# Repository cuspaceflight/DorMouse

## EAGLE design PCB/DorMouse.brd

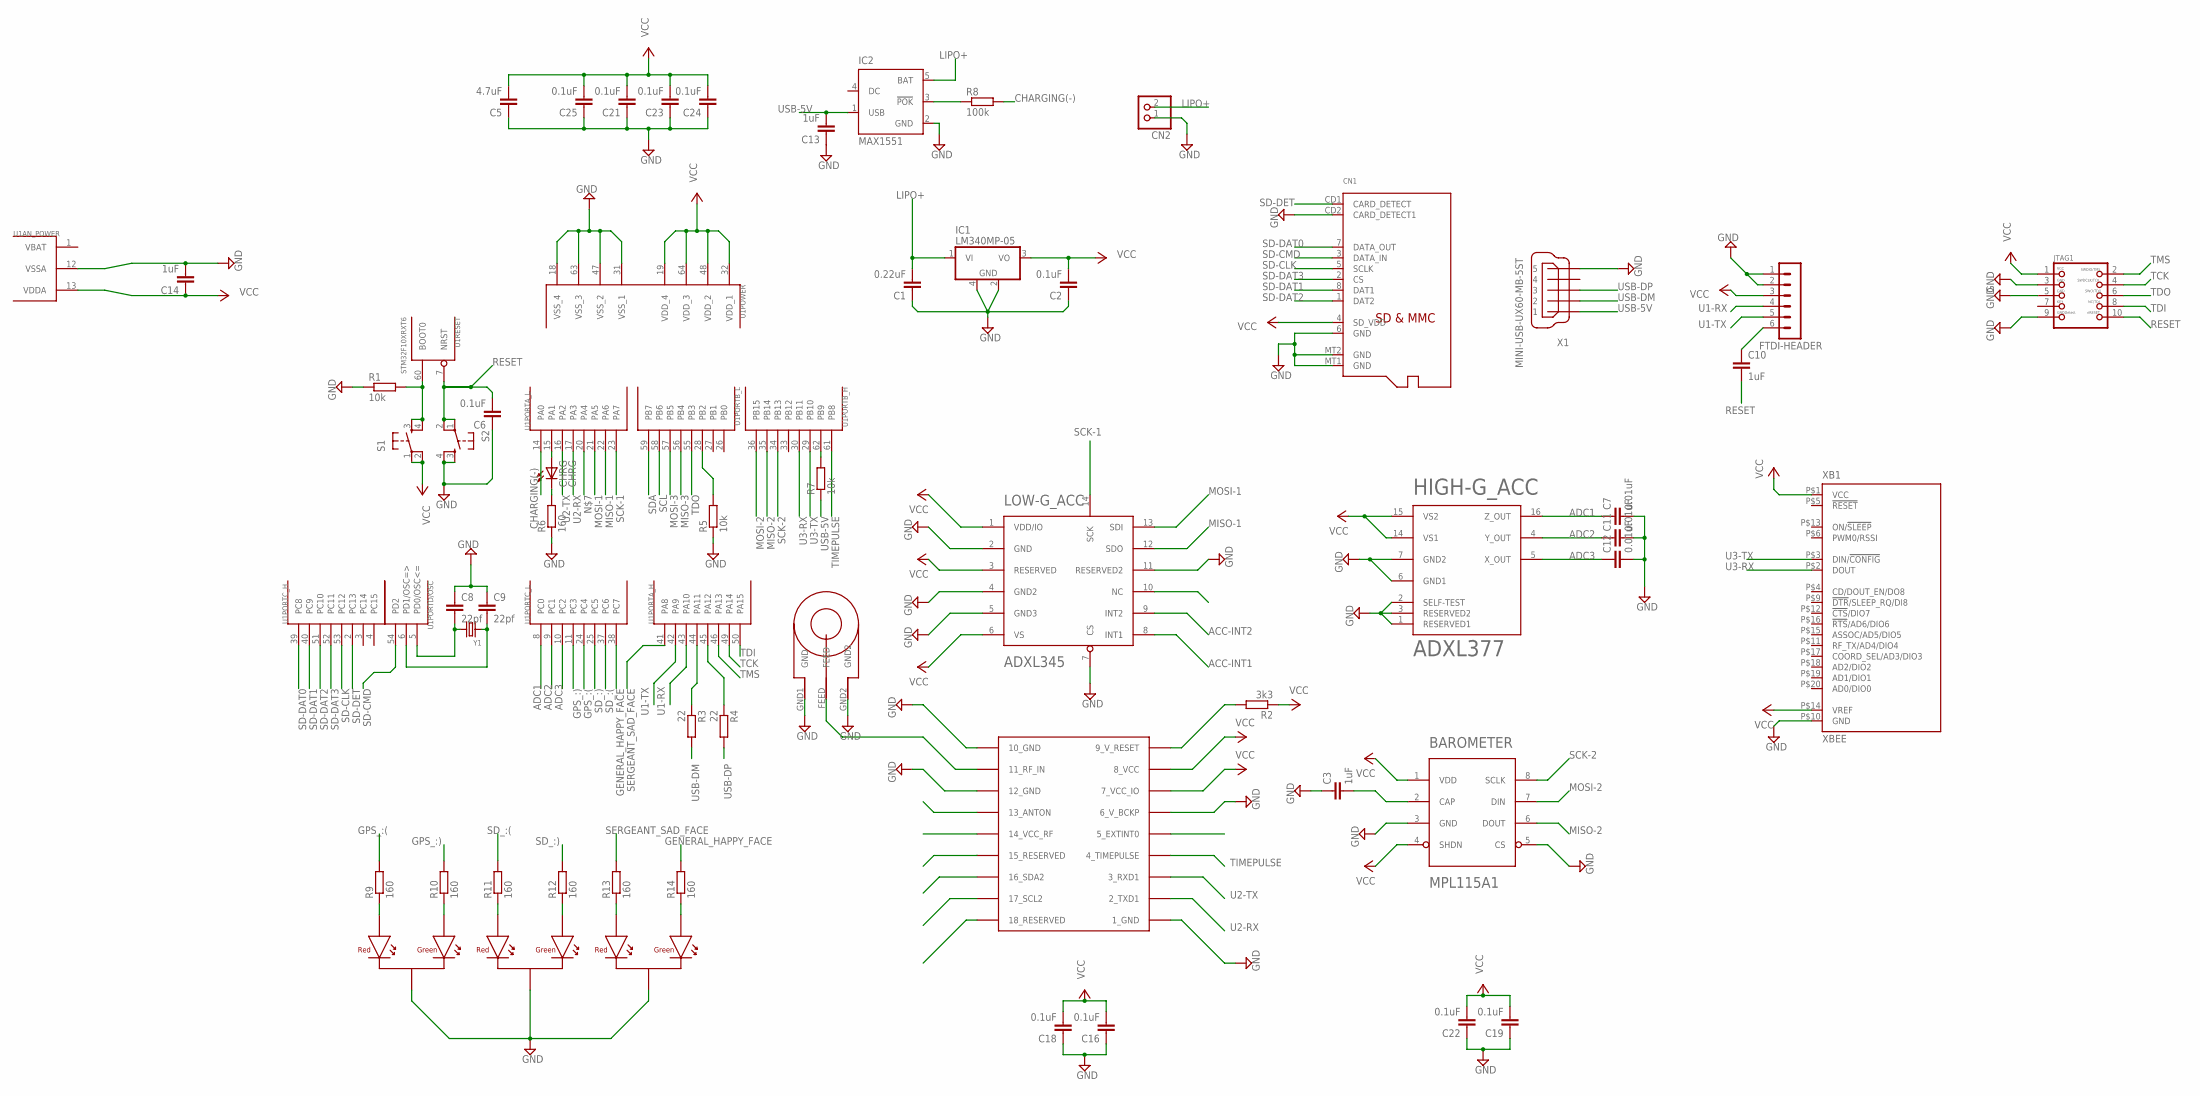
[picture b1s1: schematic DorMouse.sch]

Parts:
BAROMETER: MPL115A1; LGA-8
C1: 0.22uF; C0402
C2, C6, C16, C18, C19, C21, C22, C23, C24, C25: 0.1uF; C0402
C3, C10, C13, C14: 1uF; C0402
C5: 4.7uF; C0402
C7, C11, C12: 0.01uF; C0402
C8, C9: 22pf; C0402
CHRG: CHRG; CHIPLED_0603
CN1: MICROSD
CN2: JST_2PINSH2; JSTSH2
FTDI-HEADER: MA06-1
GENERAL: Status; SOT23
GPS: UBLOX_MAX-6
GPS-LED: GPS; SOT23
HIGH-G_ACC: ADXL377; LFCSP-16
IC1: LM340MP-05; SOT223
IC2: MAX1551; SOT23-5L
JTAG1: JTAG-CORTEXM3; 2X05_1.27MM_SMT
LOW-G_ACC: ADXL345; LGA-14
R1, R5, R7: 10k; R0402
R2: 3k3; R0402
R3, R4: 22; R0402
R6, R9, R10, R11, R12, R13, R14: 160; R0402
R8: 100k; R0402
S1, S2: TAC_SWITCHSMD; TACTILE_SWITCH_SMD
SD-LED: SD-C; SOT23
U1: STM32F10XRXT6; TQFP64
U$1: SARANTEL-SR1202
X1: MINI-USB-UX60-MB-5ST; UX60-MB-5ST
XB1: XBEE
Y1: CRYSTALSMD; HC49UP

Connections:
ACC-INT1: LOW-G_ACC.8 (INT1)
ACC-INT2: LOW-G_ACC.9 (INT2)
ADC1: C7.1, HIGH-G_ACC.16 (Z_OUT), U1.8 (PC0)
ADC2: C11.1, HIGH-G_ACC.4 (Y_OUT), U1.9 (PC1)
ADC3: C12.1, HIGH-G_ACC.5 (X_OUT), U1.10 (PC2)
BOOT1: R5.2, U1.28 (PB2)
CHARGING(-): R8.2, U1.14 (PA0)
GENERAL_HAPPY_FACE: R14.2, U1.38 (PC7)
GND: BAROMETER.3 (GND), BAROMETER.5 (CS), C1.1, C2.1, C3.1, C5.1, C6.1, C7.2, C8.1, C9.1, C11.2, C12.2, C13.1, C14.2, C16.1, C18.1, C19.1, C21.1, C22.1, C23.1, C24.1, C25.1, CN1.6 (GND), CN1.CD2 (CARD_DETECT1), CN1.MT1 (GND), CN1.MT2 (GND), CN2.1, FTDI-HEADER.1, FTDI-HEADER.2, GENERAL.3 (CATHODE), GPS.1_GND, GPS.6_V_BCKP, GPS.10_GND, GPS.12_GND, GPS-LED.3 (CATHODE), HIGH-G_ACC.1 (RESERVED1), HIGH-G_ACC.2 (SELF-TEST), HIGH-G_ACC.3 (RESERVED2), HIGH-G_ACC.6 (GND1), HIGH-G_ACC.7 (GND2), IC1.2 (GND1), IC1.4 (GND), IC2.2 (GND), JTAG1.3, JTAG1.5, JTAG1.9, LOW-G_ACC.2 (GND), LOW-G_ACC.4 (GND2), LOW-G_ACC.5 (GND3), LOW-G_ACC.7 (CS), LOW-G_ACC.11 (RESERVED2), R1.1, R5.1, R6.1, S2.3, S2.4, SD-LED.3 (CATHODE), U1.12 (VSSA), U1.18 (VSS_4), U1.31 (VSS_1), U1.47 (VSS_2), U1.63 (VSS_3), U$1.GND1 (GND), U$1.GND2, X1.5, XB1.P$10 (GND)
GPS_:(: R9.2, U1.24 (PC4)
GPS_:): R10.2, U1.11 (PC3)
LIPO+: C1.2, CN2.2, IC1.1 (VI), IC2.5 (BAT)
MISO-1: LOW-G_ACC.12 (SDO), U1.22 (PA6)
MISO-2: BAROMETER.6 (DOUT), U1.35 (PB14)
MISO-3: U1.56 (PB4)
MOSI-1: LOW-G_ACC.13 (SDI), U1.21 (PA5)
MOSI-2: BAROMETER.7 (DIN), U1.36 (PB15)
MOSI-3: U1.57 (PB5)
unnamed: R1.2, S1.3, S1.4, U1.60 (BOOT0)
unnamed: BAROMETER.2 (CAP), C3.2
unnamed: R3.1, U1.44 (PA11)
unnamed: C9.2, U1.6 (PD1/OSC=>), Y1.1
unnamed: R4.1, U1.45 (PA12)
unnamed: CHRG.A, U1.15 (PA1)
unnamed: CHRG.C, R6.2
unnamed: IC2.3 (!POK), R8.1
unnamed: C8.2, U1.5 (PD0/OSC<=), Y1.2
unnamed: GPS.9_V_RESET, R2.2
unnamed: GPS-LED.1 (RED-ANODE), R9.1
unnamed: GPS.11_RF_IN, U$1.FEED
unnamed: C10.1, FTDI-HEADER.6
unnamed: R7.2, U1.62 (PB9)
unnamed: GPS-LED.2 (GREEN-ANODE), R10.1
unnamed: R11.1, SD-LED.1 (RED-ANODE)
unnamed: R12.1, SD-LED.2 (GREEN-ANODE)
unnamed: GENERAL.1 (RED-ANODE), R13.1
unnamed: GENERAL.2 (GREEN-ANODE), R14.1
RESET: C6.2, C10.2, JTAG1.10, S2.1, S2.2, U1.7 (NRST)
SCK-1: LOW-G_ACC.14 (SCK), U1.23 (PA7)
SCK-2: BAROMETER.8 (SCLK), U1.34 (PB13)
SCL: U1.58 (PB6)
SD-CLK: CN1.5 (SCLK), U1.53 (PC12)
SD-CMD: CN1.3 (DATA_IN), U1.54 (PD2)
SD-DAT0: CN1.7 (DATA_OUT), U1.39 (PC8)
SD-DAT1: CN1.8 (DAT1), U1.40 (PC9)
SD-DAT2: CN1.1 (DAT2), U1.51 (PC10)
SD-DAT3: CN1.2 (CS), U1.52 (PC11)
SD-DET: CN1.CD1 (CARD_DETECT), U1.2 (PC13)
SDA: U1.59 (PB7)
SD_:(: R11.2, U1.37 (PC6)
SD_:): R12.2, U1.25 (PC5)
SERGEANT_SAD_FACE: R13.2, U1.41 (PA8)
TCK: JTAG1.4, U1.49 (PA14)
TDI: JTAG1.8, U1.50 (PA15)
TDO: JTAG1.6, U1.55 (PB3)
TIMEPULSE: GPS.4_TIMEPULSE, U1.61 (PB8)
TMS: JTAG1.2, U1.46 (PA13)
U1-RX: FTDI-HEADER.4, U1.43 (PA10)
U1-TX: FTDI-HEADER.5, U1.42 (PA9)
U2-RX: GPS.2_TXD1, U1.17 (PA3)
U2-TX: GPS.3_RXD1, U1.16 (PA2)
U3-RX: U1.30 (PB11), XB1.P$2 (DOUT)
U3-TX: U1.29 (PB10), XB1.P$3 (DIN/!CONFIG)
USB-5V: C13.2, IC2.1 (USB), R7.1, X1.1
USB-DM: R3.2, X1.2
USB-DP: R4.2, X1.3
VBAT: U1.1 (VBAT)
VCC: BAROMETER.1 (VDD), BAROMETER.4 (SHDN), C2.2, C5.2, C14.1, C16.2, C18.2, C19.2, C21.2, C22.2, C23.2, C24.2, C25.2, CN1.4 (SD_VDD), FTDI-HEADER.3, GPS.7_VCC_IO, GPS.8_VCC, HIGH-G_ACC.14 (VS1), HIGH-G_ACC.15 (VS2), IC1.3 (VO), JTAG1.1, LOW-G_ACC.1 (VDD/IO), LOW-G_ACC.3 (RESERVED), LOW-G_ACC.6 (VS), R2.1, S1.1, S1.2, U1.13 (VDDA), U1.19 (VDD_4), U1.32 (VDD_1), U1.48 (VDD_2), U1.64 (VDD_3), XB1.P$1 (VCC), XB1.P$14 (VREF)

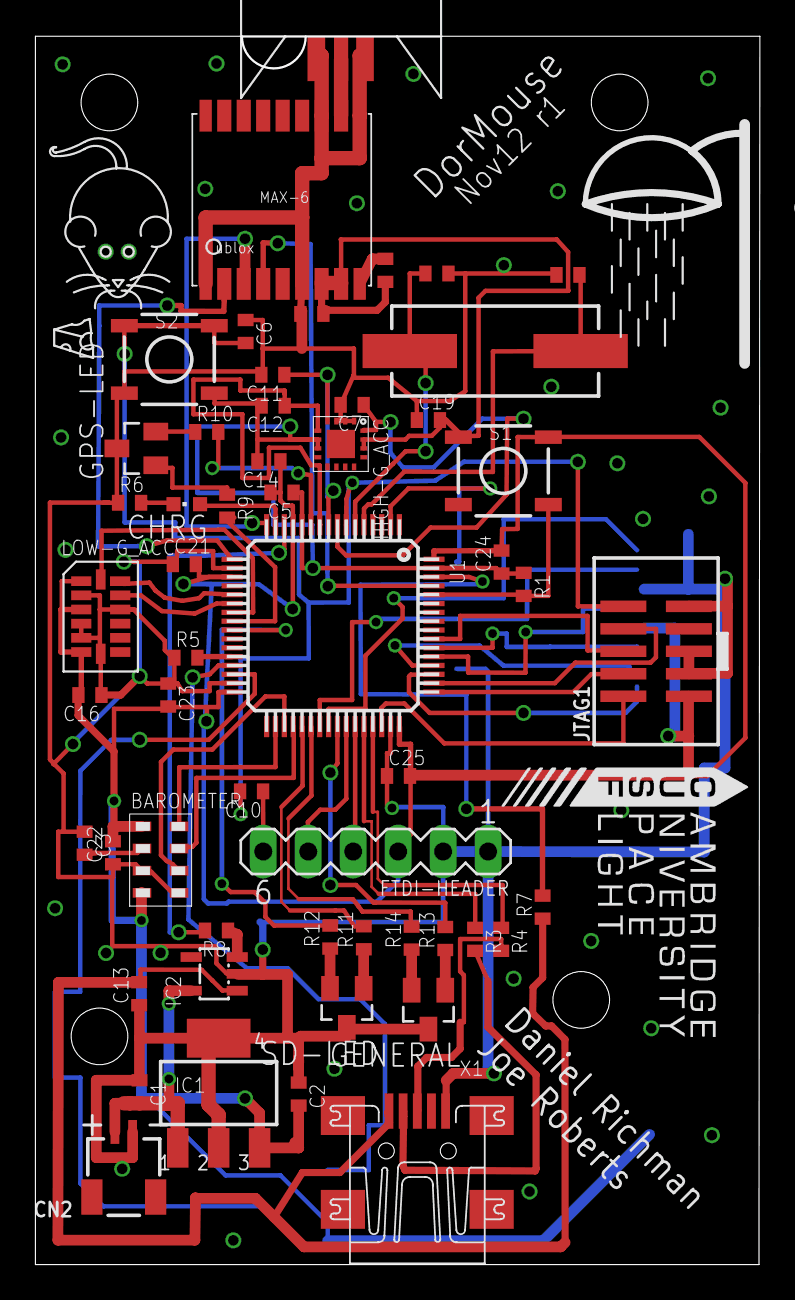
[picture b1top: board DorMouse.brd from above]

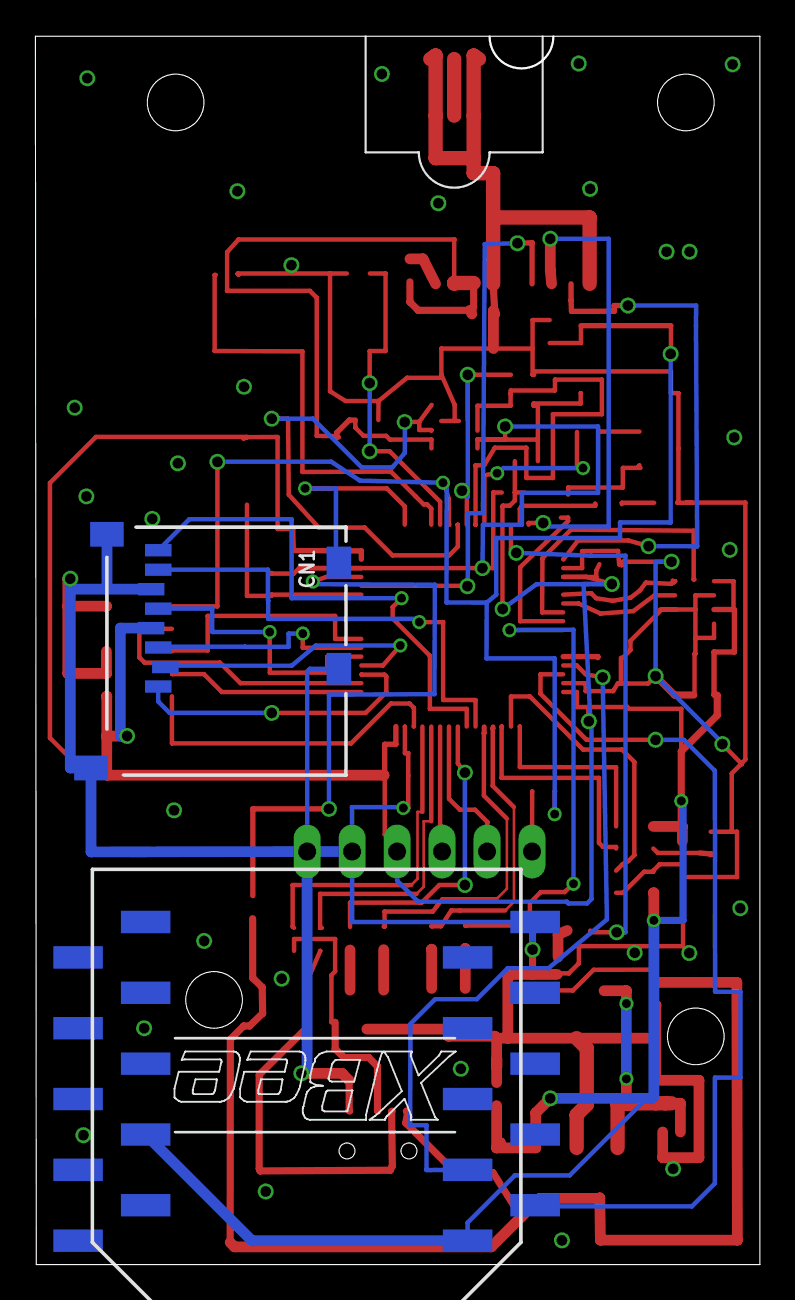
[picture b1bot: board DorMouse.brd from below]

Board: 2 copper layers, 40.9 x 69.4 mm, 59 parts (2 on the bottom side), 61 nets.

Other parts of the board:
U$2: SHOWER
U$3: DORMOUSE
U$4: CUSF_LOGO

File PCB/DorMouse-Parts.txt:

Part,Value,Device,Package,Library,Sheet
BAROMETER,MPL115A1,MPL115A1,LGA-8,DorMouse,1
C1,0.22uF,C-EUC0402,C0402,rcl,1
C2,0.1uF,C-EUC0402,C0402,rcl,1
C3,1uF,C-EUC0402,C0402,rcl,1
C5,4.7uF,C-EUC0402,C0402,rcl,1
C6,0.1uF,C-EUC0402,C0402,rcl,1
C7,0.01uF,C-EUC0402,C0402,rcl,1
C8,22pf,C-EUC0402,C0402,rcl,1
C9,22pf,C-EUC0402,C0402,rcl,1
C10,1uF,C-EUC0402,C0402,rcl,1
C11,0.01uF,C-EUC0402,C0402,rcl,1
C12,0.01uF,C-EUC0402,C0402,rcl,1
C13,1uF,C-EUC0402,C0402,rcl,1
C14,1uF,C-EUC0402,C0402,rcl,1
C16,0.1uF,C-EUC0402,C0402,rcl,1
C18,0.1uF,C-EUC0402,C0402,rcl,1
C19,0.1uF,C-EUC0402,C0402,rcl,1
C21,0.1uF,C-EUC0402,C0402,rcl,1
C22,0.1uF,C-EUC0402,C0402,rcl,1
C23,0.1uF,C-EUC0402,C0402,rcl,1
C24,0.1uF,C-EUC0402,C0402,rcl,1
C25,0.1uF,C-EUC0402,C0402,rcl,1
CHRG,CHRG,LEDCHIPLED_0603,CHIPLED_0603,led,1
CN1,-,MICROSD,MICROSD,microbuilder,1
CN2,-,JST_2PINSH2,JSTSH2,microbuilder,1
FTDI-HEADER,-,MA06-1,MA06-1,con-lstb,1
GENERAL,Status,RED-GREEN_LED,SOT23,DorMouse,1
GPS,UBLOX_MAX-6,UBLOX_MAX-6,UBLOX_MAX-6,Ava,1
GPS-LED,GPS,RED-GREEN_LED,SOT23,DorMouse,1
HIGH-G_ACC,ADXL377,ADXL377,LFCSP-16,DorMouse,1
IC1,LM340MP-05,LM340MP-05,SOT223,linear,1
IC2,MAX1551,MAX1551,SOT23-5L,maxim,1
JTAG1,-,JTAG-CORTEXM3,2X05_1.27MM_SMT,microbuilder,1
LOW-G_ACC,ADXL345,ADXL345,LGA-14,Swallow,1
R1,10k,R-EU_R0402,R0402,rcl,1
R2,3k3,R-EU_R0402,R0402,rcl,1
R3,22,R-EU_R0402,R0402,rcl,1
R4,22,R-EU_R0402,R0402,rcl,1
R5,10k,R-EU_R0402,R0402,rcl,1
R6,160,R-EU_R0402,R0402,rcl,1
R7,10k,R-EU_R0402,R0402,rcl,1
R8,100k,R-EU_R0402,R0402,rcl,1
R9,160,R-EU_R0402,R0402,rcl,1
R10,160,R-EU_R0402,R0402,rcl,1
R11,160,R-EU_R0402,R0402,rcl,1
R12,160,R-EU_R0402,R0402,rcl,1
R13,160,R-EU_R0402,R0402,rcl,1
R14,160,R-EU_R0402,R0402,rcl,1
S1,-,TAC_SWITCHSMD,TACTILE_SWITCH_SMD,SparkFun,1
S2,-,TAC_SWITCHSMD,TACTILE_SWITCH_SMD,SparkFun,1
SD-LED,SD-C,RED-GREEN_LED,SOT23,DorMouse,1
U$1,SARANTEL-SR1202,SARANTEL-SR1202,SARANTEL-SR1202,Ava,1
U1,STM32F10XRXT6,STM32F10XRXT6,TQFP64,stm32,1
X1,MINI-USB-UX60-MB-5ST,MINI-USB-UX60-MB-5ST,UX60-MB-5ST,con-hirose,1
XB1,XBEE,XBEE,XBEE,Swallow,1
Y1,-,CRYSTALSMD,HC49UP,microbuilder,1

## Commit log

2012-11-23 Silkscreen work: values and mice
2012-11-23 Gerbers run
2012-11-23 CUSF Logo
2012-11-24 Add mounting holes
2012-11-24 Add labels for GPS
2012-11-24 update partslist
2012-11-25 Connect pad 2 of LDO reg to GND
2012-11-28 SD card bits
2012-11-28 sd.c
2012-11-28 sd_buffer.h beginnings
2012-11-29 buffer.c
2012-11-29 use sdio altfn
2012-11-29 remove panic
2012-11-29 leds.c
2012-11-29 cm3_assert
2012-11-29 sd led, general led
2012-11-29 main init stuff
2012-11-29 accel_lowg
2012-11-29 accel_lowg finish
2012-11-29 baro
2012-11-29 baro fail heuristic
2012-11-29 WIP commit: accel highg
2012-11-29 accel_highg
2012-11-30 Compiling, testing, programming stuff
2012-11-30 Actually switch spi on
2012-11-30 debug
2012-11-30 debug. timer fixes. misc stuff
2012-11-30 Work in progress
2012-11-30 index on master: 099c954 Work in progress
2012-11-30 poor attempt at removing anything dma

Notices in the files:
parts and their libraries:
microbuilder: This work is placed in the public domain, and may be freely used for commercial and non-commercial work with the following conditions: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
SparkFun: Licensing: CC v3.0 Share-Alike You are welcome to use this library for commercial purposes.
